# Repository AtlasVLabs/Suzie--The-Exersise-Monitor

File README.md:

# Suzie

A wearable workout-monitoring prototype built with an ESP32 and ESP-IDF. Suzie processes sensor data to detect repetitions and track movement throughout a set, with the end goal of visualizing progress in a more quantitative and easy to understand manner.

## Current Features

- Phase-transition detection and repetition counting
- Automatic set detection with an inactivity timeout
- Rep and set duration tracking
- Per-rep range of motion and movement-effort metrics
- Set-level averages and exponential moving averages (EMA)
- Real-time debug output for signal and metric validation

Movement effort is a signal-derived metric, not a measurement of calories or mechanical work.

## Development

The project combines embedded C firmware, sensor integration, signal processing, and hardware prototyping. Rep and set metrics have been tested through live signal plots; broader workout validation is ongoing.

## Next Steps

- Transfer structured rep and set data to a host application
- Build a simple interactive terminal dashboard
- Measure detection accuracy and repeatability
- Develop a custom PCB and document board bring-up

**Status:** Active development.

---

<sub>This repository is shared for private review only. Please do not copy, redistribute, or reuse the code without permission.</sub>

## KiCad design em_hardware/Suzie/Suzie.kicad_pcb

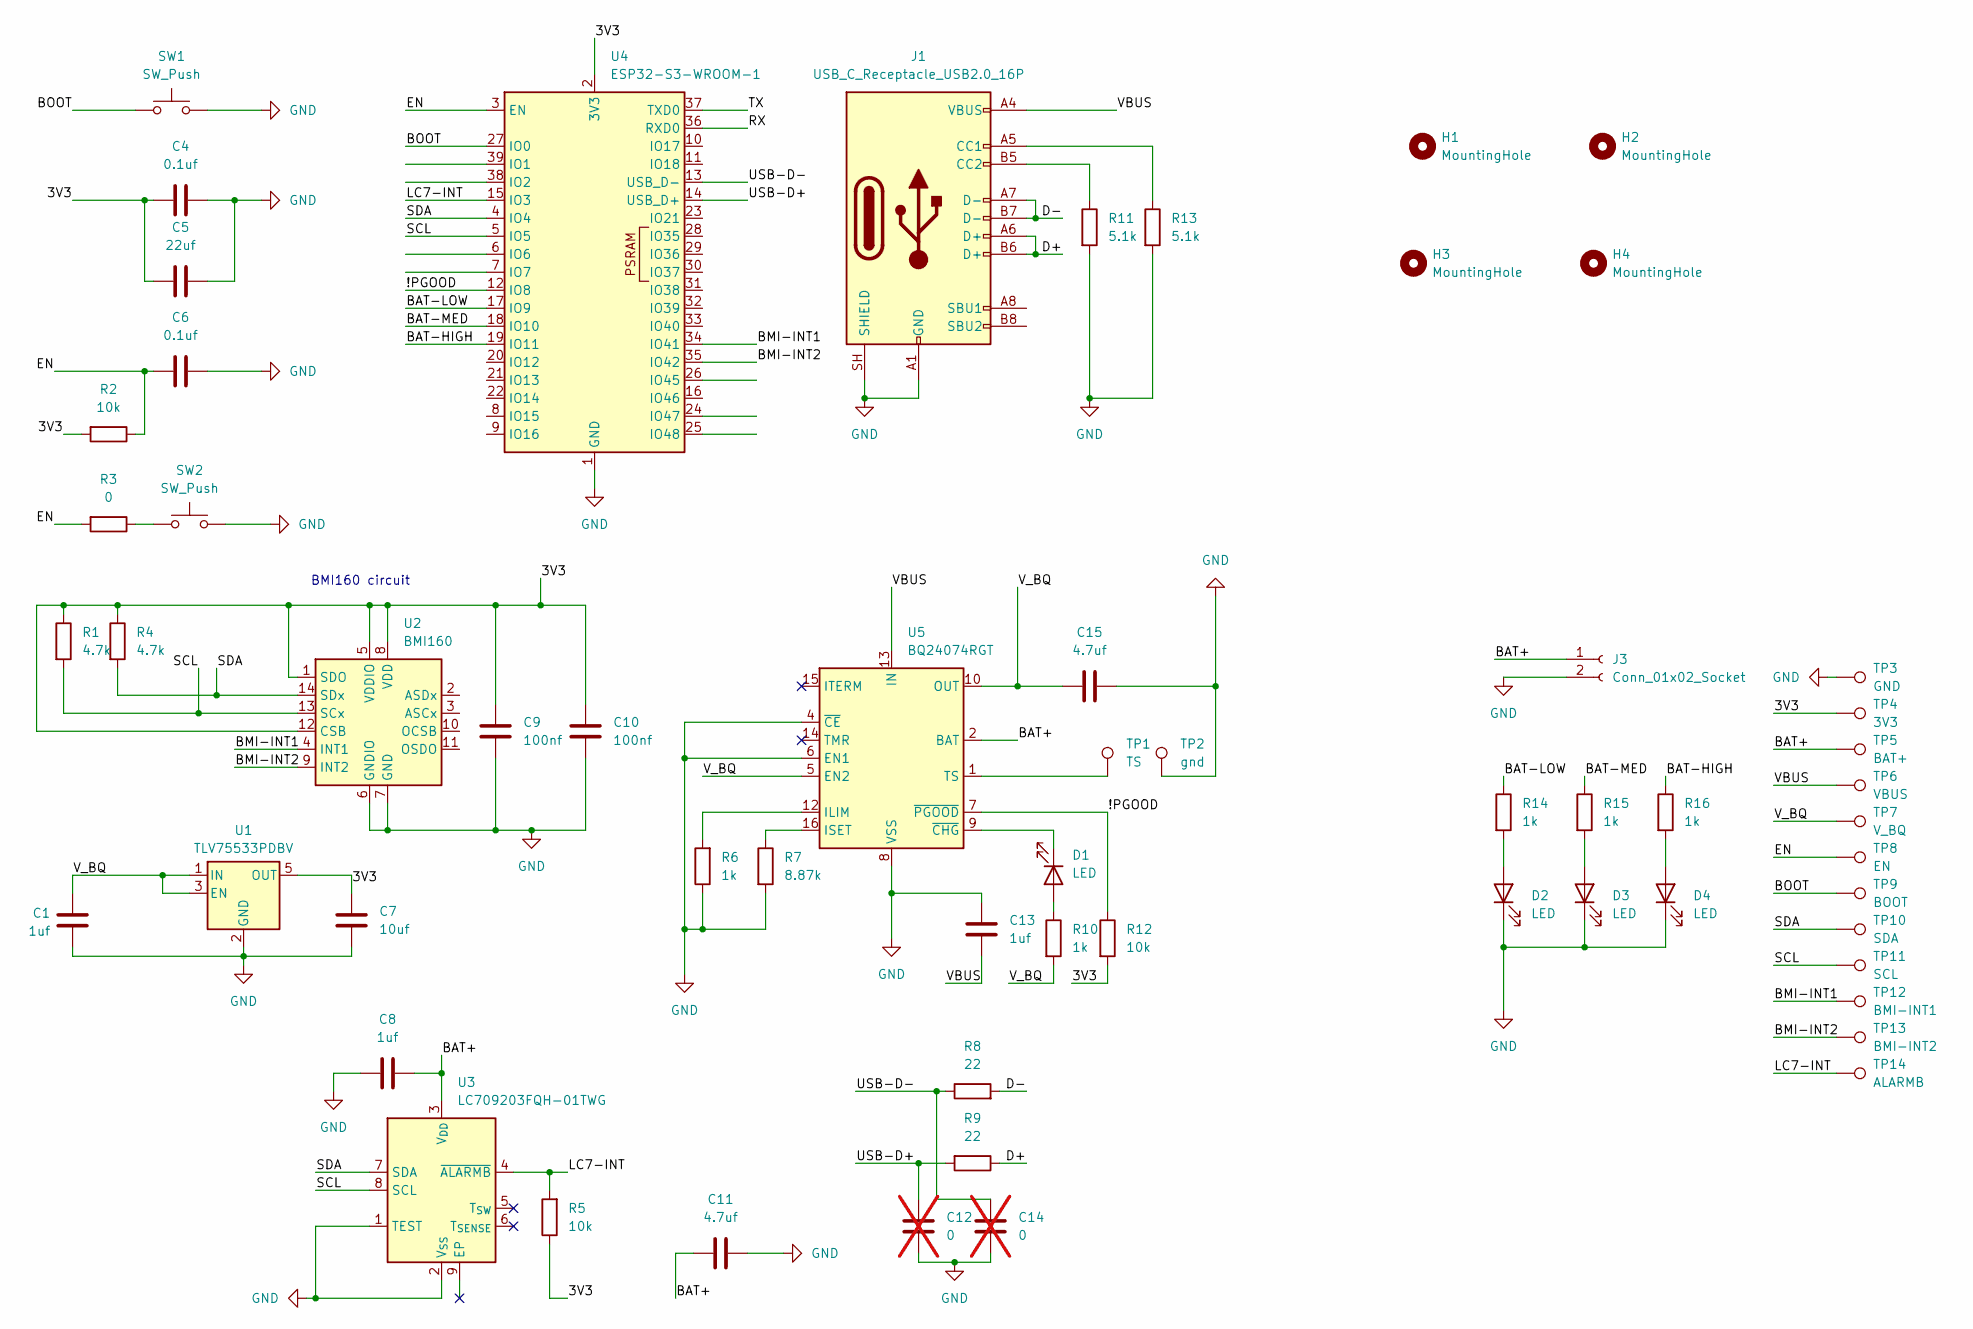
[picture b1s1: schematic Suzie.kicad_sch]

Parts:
C1, C8, C13: 1uf; C_0805_2012Metric
C4, C6: 0.1uf; C_0805_2012Metric
C5: 22uf; C_1206_3216Metric
C7: 10uf; C_0805_2012Metric
C9, C10: 100nf; C_0805_2012Metric
C11, C15: 4.7uf; C_0805_2012Metric
C12, C14: 0; C_0805_2012Metric; not fitted
D1, D2, D3, D4: LED; LED_0805_2012Metric
H1, H2, H3, H4: MountingHole; MountingHole_2.2mm_M2
J1: USB_C_Receptacle_USB2.0_16P; USB_C_Receptacle_GCT_USB4105-xx-A_16P_TopMnt_Horizontal
J3: Conn_01x02_Socket; JST_PH_S2B-PH-K_1x02_P2.00mm_Horizontal
R1, R4: 4.7k; R_0805_2012Metric
R2, R5, R12: 10k; R_0805_2012Metric
R3: 0; R_0805_2012Metric
R6, R10, R14, R15, R16: 1k; R_0805_2012Metric
R7: 8.87k; R_0805_2012Metric
R8, R9: 22; R_0805_2012Metric
R11, R13: 5.1k; R_0805_2012Metric
SW1, SW2: SW_Push; SW_SPST_TL3342
TP1: TS; TestPoint_Pad_1.0x1.0mm
TP2: gnd; TestPoint_Pad_1.0x1.0mm
TP3: GND; TestPoint_Pad_1.0x1.0mm
TP4: 3V3; TestPoint_Pad_1.0x1.0mm
TP5: BAT+; TestPoint_Pad_1.0x1.0mm
TP6: VBUS; TestPoint_Pad_1.0x1.0mm
TP7: V_BQ; TestPoint_Pad_1.0x1.0mm
TP8: EN; TestPoint_Pad_1.0x1.0mm
TP9: BOOT; TestPoint_Pad_1.0x1.0mm
TP10: SDA; TestPoint_Pad_1.0x1.0mm
TP11: SCL; TestPoint_Pad_1.0x1.0mm
TP12: BMI-INT1; TestPoint_Pad_1.0x1.0mm
TP13: BMI-INT2; TestPoint_Pad_1.0x1.0mm
TP14: ALARMB; TestPoint_Pad_1.0x1.0mm
U1: TLV75533PDBV; SOT-23-5
U2: BMI160; Bosch_LGA-14_3x2.5mm_P0.5mm
U3: LC709203FQH-01TWG; WDFN-8-1EP_4x3mm_P0.65mm_EP2.4x1.8mm
U4: ESP32-S3-WROOM-1
U5: BQ24074RGT; VQFN-16-1EP_3x3mm_P0.5mm_EP1.6x1.6mm

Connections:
/3V3: C4.2, C5.2, C7.1, C9.1, C10.1, R1.1, R2.2, R4.1, R5.1, R12.2, TP4.1 (1_1), U1.5 (OUT), U2.1 (SDO), U2.5 (VDDIO), U2.8 (VDD), U2.12 (CSB), U4.2 (3V3)
/!PGOOD: R12.1, U4.12 (IO8), U5.7 (~PGOOD)
/BAT+: C8.2, C11.1, J3.1, TP5.1 (1_1), U3.3 (V_{DD}), U5.2 (BAT), U5.3 (BAT)
/BAT-HIGH: R16.1, U4.19 (IO11)
/BAT-LOW: R14.1, U4.17 (IO9)
/BAT-MED: R15.1, U4.18 (IO10)
/BMI-INT1: TP12.1 (1_1), U2.4 (INT1), U4.34 (IO41)
/BMI-INT2: TP13.1 (1_1), U2.9 (INT2), U4.35 (IO42)
/BOOT: SW1.1, TP9.1 (1_1), U4.27 (IO0)
/D+: J1.A6 (D+), J1.B6 (D+), R9.1
/D-: J1.A7 (D-), J1.B7 (D-), R8.2
/EN: C6.2, R2.1, R3.2, TP8.1 (1_1), U4.3 (EN)
/LC7-INT: R5.2, TP14.1 (1_1), U3.4 (~ALARMB), U4.15 (IO3)
/RX: U4.36 (RXD0)
/SCL: R1.2, TP11.1 (1_1), U2.13 (SCx), U3.8 (SCL), U4.5 (IO5)
/SDA: R4.2, TP10.1 (1_1), U2.14 (SDx), U3.7 (SDA), U4.4 (IO4)
/TX: U4.37 (TXD0)
/USB-D+: C12.1, R9.2, U4.14 (USB_D+)
/USB-D-: C14.1, R8.1, U4.13 (USB_D-)
/VBUS: C13.2, J1.A4 (VBUS), J1.A9 (VBUS), J1.B4 (VBUS), J1.B9 (VBUS), TP6.1 (1_1), U5.13 (IN)
/V_BQ: C1.2, C15.1, R10.2, TP7.1 (1_1), U1.1 (IN), U1.3 (EN), U5.5 (EN2), U5.10 (OUT), U5.11 (OUT)
GND: C1.1, C4.1, C5.1, C6.1, C7.2, C8.1, C9.2, C10.2, C11.2, C12.2, C13.1, C14.2, C15.2, D2.1 (K), D3.1 (K), D4.1 (K), J1.A1 (GND), J1.A12 (GND), J1.B1 (GND), J1.B12 (GND), J1.SH (SHIELD), J3.2, R6.1, R7.2, R11.2, R13.2, SW1.2, SW2.2, TP2.1 (1_1), TP3.1 (1_1), U1.2 (GND), U2.6 (GNDIO), U2.7 (GND), U3.1 (TEST), U3.2 (V_{SS}), U4.1 (GND), U4.40 (GND), U4.41 (GND), U5.4 (~CE), U5.6 (EN1), U5.8 (VSS), U5.17 (VSS)
unnamed: D1.2 (A), R10.1
unnamed: D1.1 (K), U5.9 (~CHG)
unnamed: D2.2 (A), R14.2
unnamed: D3.2 (A), R15.2
unnamed: D4.2 (A), R16.2
unnamed: J1.A5 (CC1), R13.1
unnamed: J1.B5 (CC2), R11.1
unnamed: R3.1, SW2.1
unnamed: R6.2, U5.12 (ILIM)
unnamed: R7.1, U5.16 (ISET)
unnamed: TP1.1 (1_1), U5.1 (TS)

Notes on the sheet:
BMI160 circuit

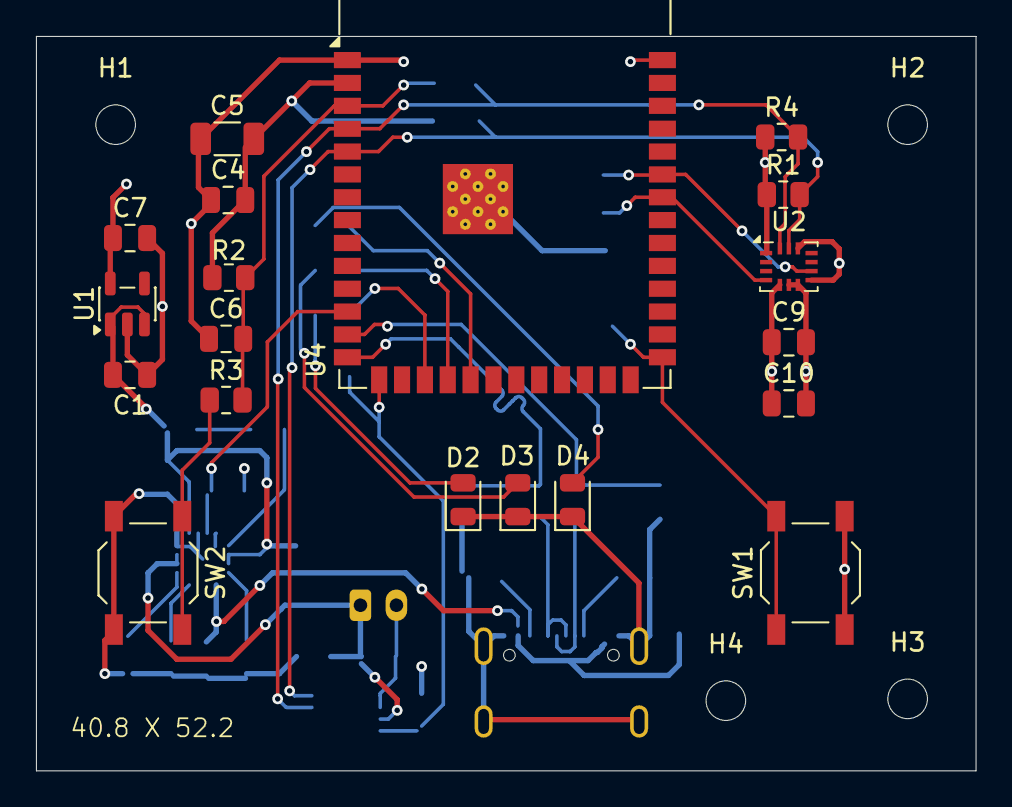
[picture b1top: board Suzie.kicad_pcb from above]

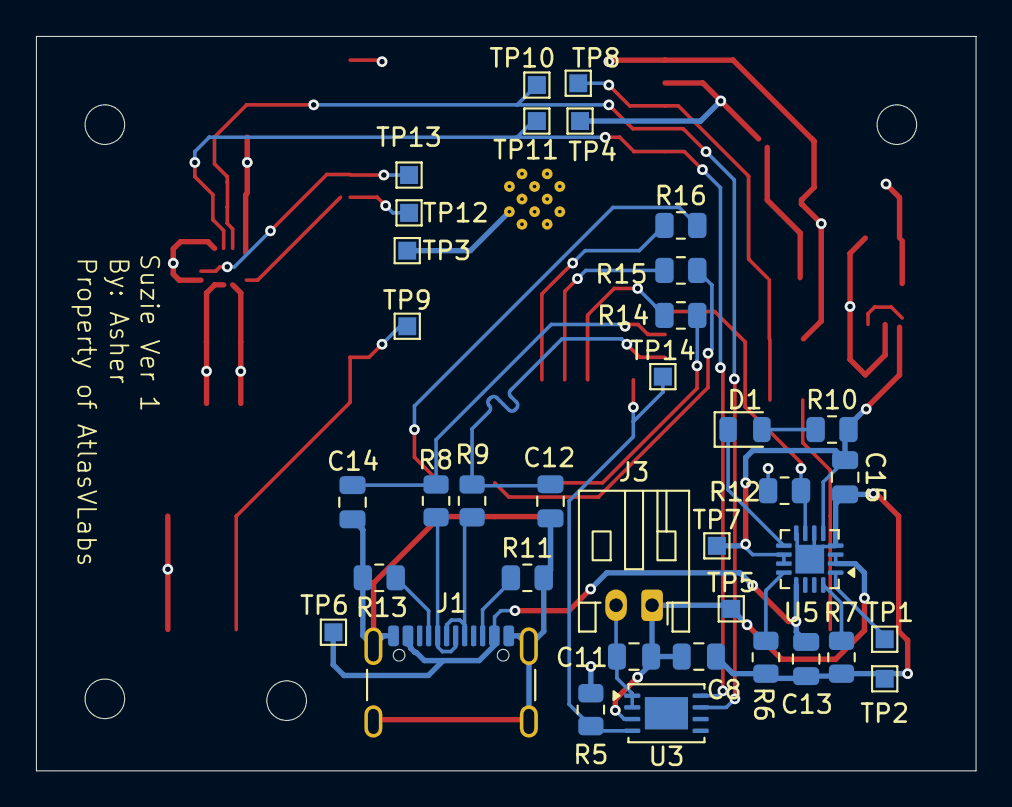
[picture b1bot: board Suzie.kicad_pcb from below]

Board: 4 copper layers, 52.2 x 40.8 mm, 60 parts (37 on the bottom side), 31 nets.

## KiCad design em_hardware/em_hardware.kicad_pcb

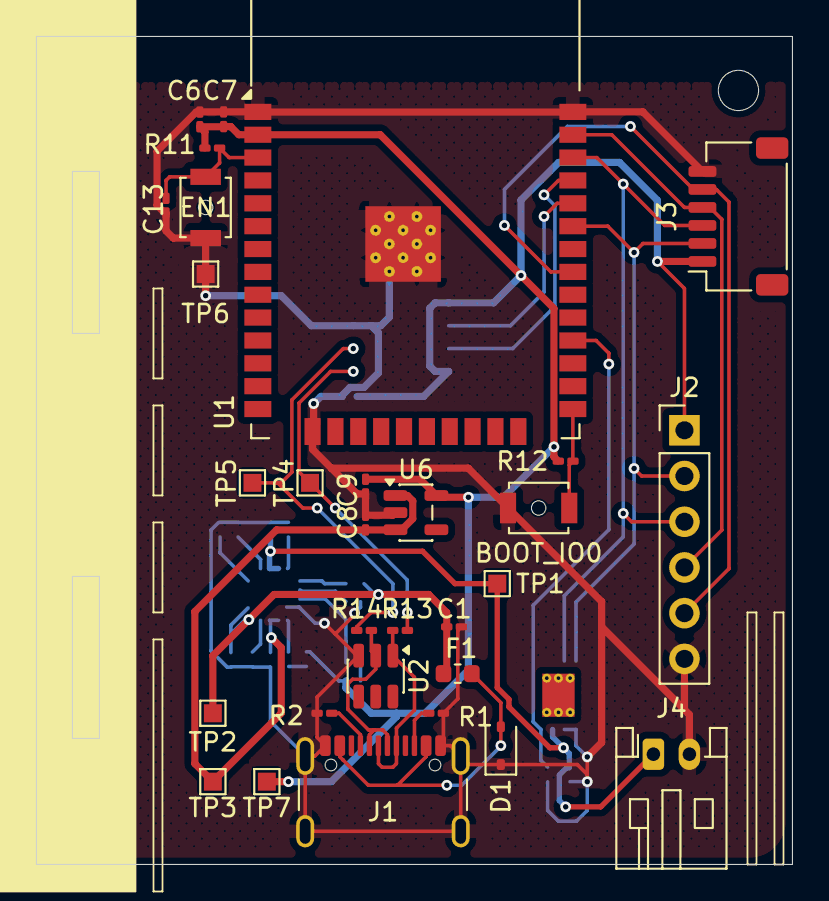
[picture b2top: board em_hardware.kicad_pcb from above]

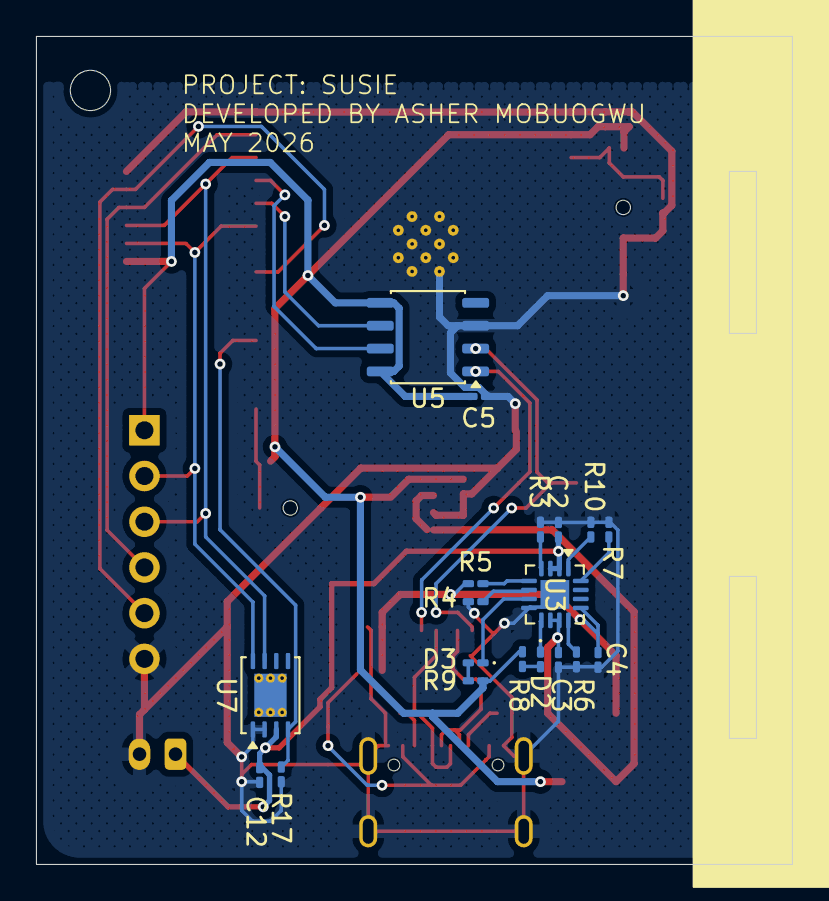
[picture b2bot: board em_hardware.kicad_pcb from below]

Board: 2 copper layers, 42.0 x 46.0 mm, 49 parts (19 on the bottom side), 31 nets.

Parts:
BOOT_IO0: SW_Push; SW_SPST_B3U-1000P-B
C1, C8, C9: 10uf; C_0201_0603Metric_Pad0.64x0.40mm_HandSolder
C2, C3, C4, C5: 4.7uf; C_0201_0603Metric_Pad0.64x0.40mm_HandSolder
C6: 0.1uf; C_0201_0603Metric_Pad0.64x0.40mm_HandSolder
C7, C12, C13: 1uf; C_0201_0603Metric_Pad0.64x0.40mm_HandSolder
D1: SD05C-01F; D_SOD-323
D2: RED_LED; LED_0201_0603Metric_Pad0.64x0.40mm_HandSolder
D3: GREEN_LED; LED_0201_0603Metric_Pad0.64x0.40mm_HandSolder
EN1: SW_Push; SW_SPST_B3U-1000P-B
F1: Fuse; Fuse_0603_1608Metric
J1: USB_C_Receptacle_USB2.0_16P; USB_C_Receptacle_GCT_USB4105-xx-A_16P_TopMnt_Horizontal
J2: Conn_01x06_Pin; PinHeader_1x06_P2.54mm_Vertical
J3: Conn_01x06_Pin; JST_SH_SM06B-SRSS-TB_1x06-1MP_P1.00mm_Horizontal
J4: Conn_01x02_Socket; JST_PH_S2B-PH-K_1x02_P2.00mm_Horizontal
R1, R2: 5.1k; R_0201_0603Metric_Pad0.64x0.40mm_HandSolder
R3, R10, R11, R12, R17: 10k; R_0201_0603Metric_Pad0.64x0.40mm_HandSolder
R4, R5: 0; R_0201_0603Metric_Pad0.64x0.40mm_HandSolder
R6: 2k; R_0201_0603Metric_Pad0.64x0.40mm_HandSolder
R7: 1.5k; R_0201_0603Metric_Pad0.64x0.40mm_HandSolder
R8, R9: 2.2k; R_0201_0603Metric_Pad0.64x0.40mm_HandSolder
R13, R14: 22; R_0201_0603Metric_Pad0.64x0.40mm_HandSolder
TP1: BAT_TP; TestPoint_Pad_1.0x1.0mm
TP2: 5V_TP; TestPoint_Pad_1.0x1.0mm
TP3: PWR_TP; TestPoint_Pad_1.0x1.0mm
TP4: D+_TP; TestPoint_Pad_1.0x1.0mm
TP5: D-_TP; TestPoint_Pad_1.0x1.0mm
TP6: GND_TP; TestPoint_Pad_1.0x1.0mm
TP7: 3V3_TP; TestPoint_Pad_1.0x1.0mm
U1: ESP32-WROOM-32
U2: TPD2EUSB30; SOT-23-6
U3: BQ24074RGT; VQFN-16-1EP_3x3mm_P0.5mm_EP1.6x1.6mm
U5: CH340N; JEITA_SOIC-8_3.9x4.9mm_P1.27mm
U6: AP2112K-3.3; SOT-23-5
U7: LC709203FQH-01TWG; WDFN-8-1EP_4x3mm_P0.65mm_EP2.4x1.8mm_ThermalVias

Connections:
3v3: C5.1, C6.1, C7.1, C9.1, J2.1, J3.1, R8.2, R9.2, R11.2, R12.2, TP7.1 (1_1), U1.2 (VDD), U5.5 (VCC), U5.8 (V3), U6.5 (VOUT)
AUX: J2.5, J3.5, U1.31 (IO19)
BAT+: C2.1, C12.2, J4.1, TP1.1 (1_1), U3.2 (BAT), U3.3 (BAT), U7.3 (V_{DD})
D+: R13.2, TP4.1 (1_1), U5.1 (UD+)
D-: R14.2, TP5.1 (1_1), U5.2 (UD-)
GND: BOOT_IO0.2, C1.2, C2.2, C3.1, C4.1, C5.2, C6.2, C7.2, C8.2, C9.2, C12.1, C13.2, D1.1 (A1), EN1.1, J1.A1 (GND), J1.A12 (GND), J1.B1 (GND), J1.B12 (GND), J1.SH (SHIELD), J2.6, J3.6, J4.2, R1.2, R2.2, R3.2, R4.2, R6.2, R7.2, R10.2, R17.2, TP6.1 (1_1), U1.1 (GND), U1.15 (GND), U1.38 (GND), U1.39 (GND), U2.3 (GND), U3.8 (VSS), U3.17 (VSS), U5.3 (GND), U6.2 (GND), U7.1 (TEST), U7.2 (V_{SS})
INT: J2.4, J3.4, U1.37 (IO23)
LC7_INT: R17.1, U1.28 (IO17), U7.4 (~ALARMB)
unnamed: D1.2 (A2), F1.1, J1.A4 (VBUS), J1.A9 (VBUS), J1.B4 (VBUS), J1.B9 (VBUS)
unnamed: D2.2 (A), R8.1
unnamed: D2.1 (K), U3.9 (~CHG)
unnamed: D3.2 (A), R9.1
unnamed: D3.1 (K), U3.7 (~PGOOD)
unnamed: J1.A5 (CC1), R2.1
unnamed: J1.B5 (CC2), R1.1
unnamed: C13.1, EN1.2, R11.1, U1.3 (EN)
unnamed: BOOT_IO0.1, R12.1, U1.25 (IO0)
unnamed: J1.A6 (D+), J1.B6 (D+), R13.1, U2.1 (D+)
unnamed: J1.A7 (D-), J1.B7 (D-), R14.1, U2.2 (D-)
unnamed: R4.1, U3.6 (EN1)
unnamed: R5.1, U3.5 (EN2)
unnamed: R6.1, U3.12 (ILIM)
unnamed: R7.1, U3.16 (ISET)
unnamed: R10.1, U3.1 (TS)
unnamed: R3.1, U3.4 (~CE)
PWR_RAIL: C3.2, C8.1, TP3.1 (1_1), U3.10 (OUT), U3.11 (OUT), U6.1 (VIN), U6.3 (EN)
RX0: U1.34 (RXD0/IO3), U5.6 (TXD)
SCL: J2.2, J3.2, U1.33 (IO21), U7.8 (SCL)
SDA: J2.3, J3.3, U1.36 (IO22), U7.7 (SDA)
TX0: U1.35 (TXD0/IO1), U5.7 (RXD)
USB_5V_PROTECTED: C1.1, C4.2, F1.2, R5.2, TP2.1 (1_1), U3.13 (IN)

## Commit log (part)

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2026-05-04 designed the power system and battery management modules
    to do:
    led indicators for charging and valid connection
    3v reg
2026-05-05 done the power
    sensors next
2026-05-07 making this a lot smaller and adding modules
2026-05-07 almost done the PCB
2026-05-08 PCB DESIGN IS DONE
    Susie is alive
2026-05-08 added gnd shielding
2026-05-10 updates to PCB
2026-05-11 finish up the i2c lib
2026-05-12 something is wrong with our file
    remake this
2026-05-13 stuff
2026-05-15 finish up the max config function
    helpppppppppppppppppp
2026-05-17 finish up the max30102 config
2026-05-18 shutdown logic done
2026-05-19 max30102 functional
2026-05-23 bmi lib created
2026-05-26 format changes
2026-05-27 accel and gyro power mode init code created
2026-05-29 can read accel values
2026-06-03 idk yet
2026-06-04 should work
2026-06-08 can count peaks for rep detection. Needs cleaning up though
2026-06-08 deleted the old folder
2026-06-08 bug found
    p_count starts as 1. must be cuz of the a_abs
2026-06-09 proper peak detection with adequate cutoff
    fixed weird peak bug
2026-06-09 rudimentary rep count logic implemented
2026-06-09 rep detection update
    rep detection works but doesn't work as well if motion is too soft
2026-06-10 implemented rep decay
    if u hold half a rep for too long it decays. Needs fine tuning
2026-06-15 changed the rep decay time to be longer
2026-06-17 modularizing code
2026-06-23 Add private review notice to README
    Added a notice regarding private review and code usage.
2026-06-23 peak detection function
    make sure to split up the params from the outputs
2026-06-23 sig processing done.
    Work the functions into the main code
